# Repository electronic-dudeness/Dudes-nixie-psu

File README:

This is a schematic for a circuit to drive Nixie tubes at around 120-250V. It was created based on the schematic found here:
http://threeneurons.wordpress.com/nixie-power-supply/
Feel free to use it, modifiy it or feed it to your dog. It is provided "as is", so I cannot be held liable.

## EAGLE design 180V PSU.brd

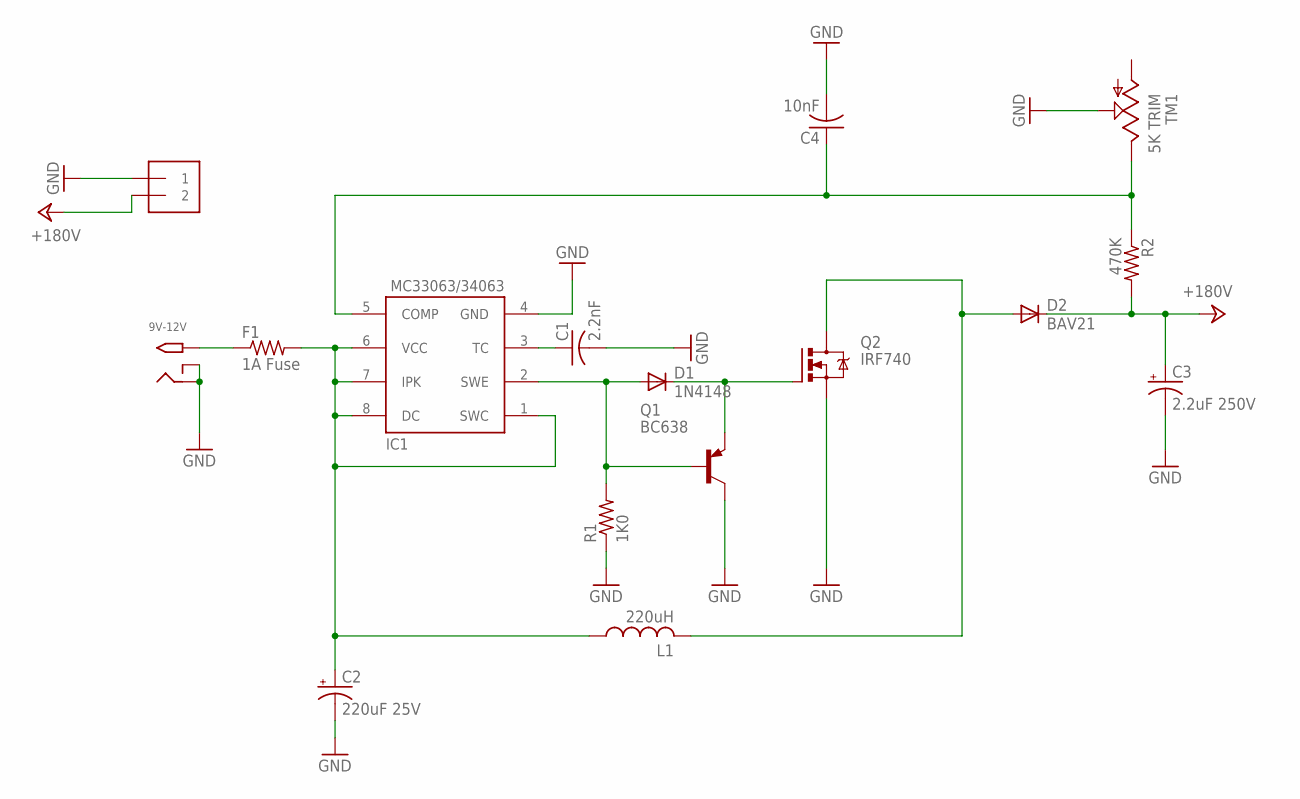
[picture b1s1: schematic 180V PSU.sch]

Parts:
9V-12V: 2.1MMJACKTHM; PJ-102A
C1: 2.2nF; C025-030X050
C2: 220uF 25V; E2,5-6
C3: 2.2uF 250V; E2,5-6
C4: 10nF; C025-030X050
D1: 1N4148; DO35-10
D2: BAV21; DO35-10
F1: 1A Fuse; 0204/5
IC1: MC33063/MC34063P; DIL08
J1: 1X2-3.5MM
L1: 220uH; 6000-XXXX-RC
Q1: BC638; TO92-BCE
Q2: IRF740; TO220BV
R1: 1K0; 0207/10
R2: 470K; 0207/10
TM1: 5K TRIM; 6MM

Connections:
+24V: C3.+, D2.C, J1.2, R2.2
GND: 9V-12V.RING, 9V-12V.RING_SW, C1.2, C2.-, C3.-, C4.2, IC1.4 (GND), J1.1, Q1.C, Q2.S, R1.1, TM1.S
unnamed: 9V-12V.TIP, F1.1
unnamed: D2.A, L1.2, Q2.D
unnamed: D1.A, IC1.2 (SWE), Q1.B, R1.2
unnamed: D1.C, Q1.E, Q2.G
unnamed: C4.1, IC1.5 (COMP), R2.1, TM1.E
unnamed: C1.1, IC1.3 (TC)
unnamed: C2.+, F1.2, IC1.1 (SWC), IC1.6 (VCC), IC1.7 (IPK), IC1.8 (DC), L1.1

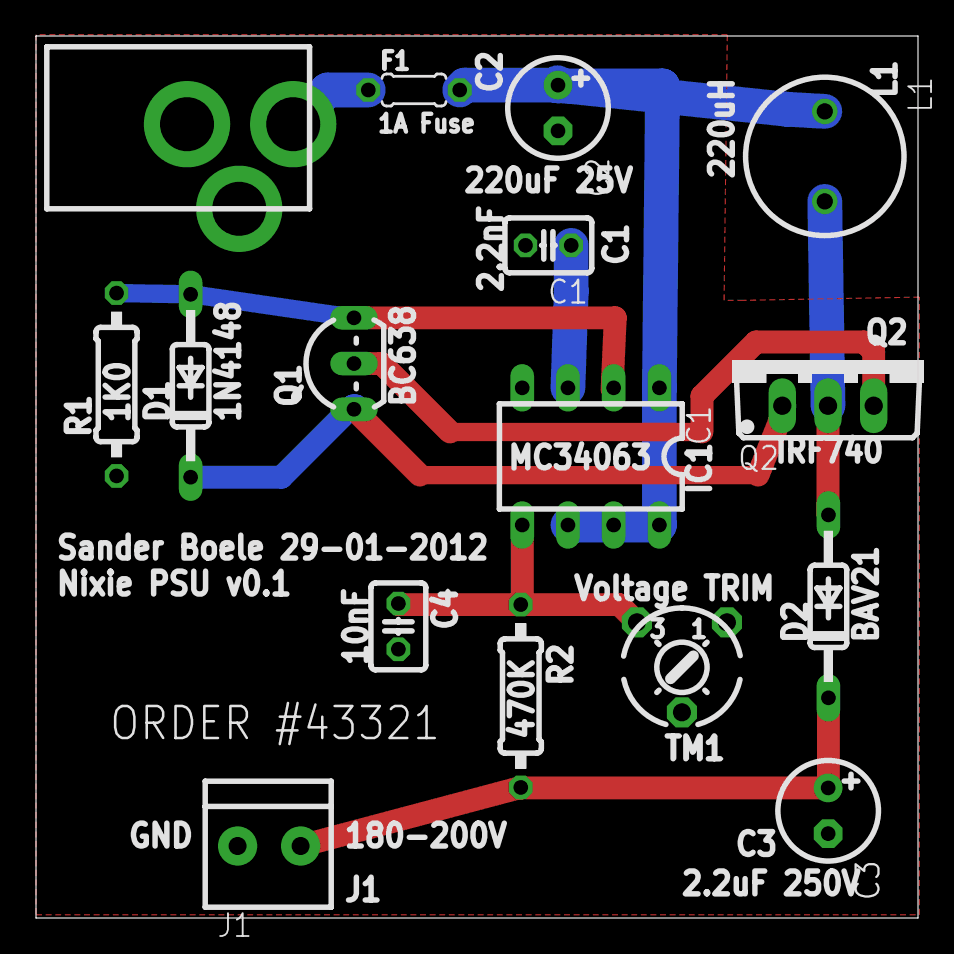
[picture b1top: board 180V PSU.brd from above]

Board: 2 copper layers, 49.0 x 49.0 mm, 16 parts (0 on the bottom side), 9 nets.
